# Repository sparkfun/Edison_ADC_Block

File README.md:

SparkFun Block for Intel Edison - ADC
==================================================

[*SparkFun Block for Intel Edison - ADC (DEV-13770)*](https://www.sparkfun.com/products/13770)

This card adds ADC functionality to the Edison's I<sup>2</sup>C bus. 
The ADS1015 ADC from TI provides a single 12-bit delta-sigma convertor with an analog multiplexer. 
It can be configured as a four-channel single-ended device or as a two-channel differential device.

The board has jumpers to allow selection of the I<sup>2</sup>C slave address among four different options, allowing up to four of these cards to be stacked under one Edison. 
The sampling rate is not sufficient for audio capture, at 2.2kHz, but it should be adequate for most control applications.

Repository Contents
-------------------

* **/Hardware** - Eagle design files (.brd, .sch)
* **/Production** - Production panel files (.brd)

Documentation
--------------

* **[Hookup Guide](https://learn.sparkfun.com/tutorials/sparkfun-blocks-for-intel-edison---adc-v20)** - Basic hookup guide for the Edison ADC Block.
* **[SparkFun Fritzing repo](https://github.com/sparkfun/Fritzing_Parts)** - Fritzing diagrams for SparkFun products.
* **[SparkFun 3D Model repo](https://github.com/sparkfun/3D_Models)** - 3D models of SparkFun products. 

Version History
---------------
* [v21](https://github.com/sparkfun/Edison_ADC_Block/tree/V_2.1) - Version 2.1. Currently for sale. Fixes noise on the ADC lines, adds locking header footprint. 
* [v20](https://github.com/sparkfun/Edison_ADC_Block/tree/V_2.0) - Version 2.0. Retired. 
* [v10](https://github.com/sparkfun/Edison_ADC_Block/tree/v10) - Original release. Retired.

License Information
-------------------

This product is _**open source**_! 

Please review the LICENSE.md file for license information. 

If you have any questions or concerns on licensing, please contact techsupport@sparkfun.com.

Distributed as-is; no warranty is given.

- Your friends at SparkFun.

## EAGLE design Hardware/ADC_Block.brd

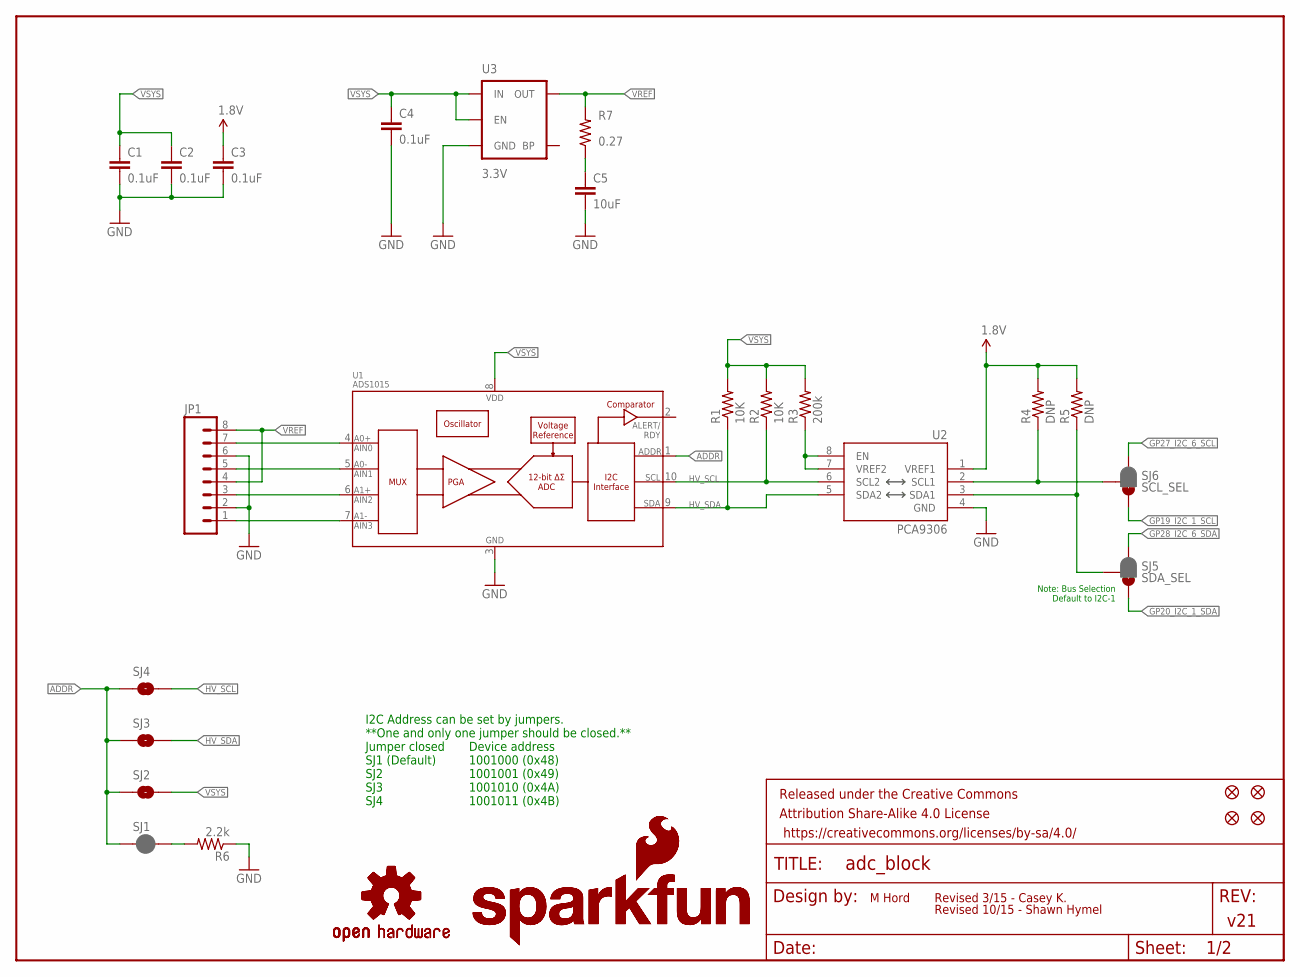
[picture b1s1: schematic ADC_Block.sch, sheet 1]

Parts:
C1, C2, C3, C4: 0.1uF; 0603-CAP
C5: 10uF; 0805-CAP
FID1, FID2, FID3, FID4: FIDUCIAL1X2; FIDUCIAL-1X2
FRAME1: FRAME-LETTER; CREATIVE_COMMONS
JP1: M08LOCK; 1X08_LOCK
LOGO1, LOGO3: SFE_LOGO_NAME_FLAME.1_INCH; SFE_LOGO_NAME_FLAME_.1
LOGO2, LOGO4: OSHW-LOGOS; OSHW-LOGO-S
R1, R2: 10K; 0603-RES
R3: 200k; 0603-RES
R4, R5: DNP; 0603-RES
R6: 2.2k; 0603-RES
R7: 0.27; 0603-RES
SJ1: JUMPER-PAD-2-NC_BY_PASTE; PAD-JUMPER-2-NC_BY_PASTE_YES_SILK
SJ2, SJ3, SJ4: JUMPER-PAD-2-NOYES_SILK; PAD-JUMPER-2-NO_YES_SILK
SJ5: SDA_SEL; PAD-HUMPER-3-1&2_NC_BY_PASTE_YES_SILK_FULL_BOX
SJ6: SCL_SEL; PAD-HUMPER-3-1&2_NC_BY_PASTE_YES_SILK_FULL_BOX
U1: ADS1015; MSOP10
U2: PCA9306; PCA9306DC-1:1
U3: 3.3V; SOT23-5

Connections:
1.8V: C3.1, R4.2, R5.2, U2.1 (VREF1); also elsewhere on the board
A0+/AIN0: JP1.7, U1.4 (AIN0)
A0-/AIN1: JP1.5, U1.5 (AIN1)
A1+/AIN2: JP1.3, U1.6 (AIN2)
A1-/AIN3: JP1.1, U1.7 (AIN3)
ADDR: SJ1.1, SJ2.1, SJ3.1, SJ4.1, U1.1 (ADDR)
GND: C1.2, C2.2, C3.2, C4.2, C5.2, JP1.2, JP1.6, R6.1, U1.3 (VSS), U2.4 (GND), U3.2 (GND); also elsewhere on the board
GP19_I2C_1_SCL: SJ6.3; also elsewhere on the board
GP20_I2C_1_SDA: SJ5.3; also elsewhere on the board
GP27_I2C_6_SCL: SJ6.1; also elsewhere on the board
GP28_I2C_6_SDA: SJ5.1; also elsewhere on the board
HV_SCL: R2.1, SJ4.2, U1.10 (SCL), U2.6 (SCL2)
HV_SDA: R1.1, SJ3.2, U1.9 (SDA), U2.5 (SDA2)
unnamed: R3.1, U2.7 (VREF2), U2.8 (EN)
unnamed: R4.1, SJ6.2, U2.2 (SCL1)
unnamed: R6.2, SJ1.2
unnamed: R5.1, SJ5.2, U2.3 (SDA1)
unnamed: C5.1, R7.1
VREF: JP1.4, JP1.8, R7.2, U3.5 (OUT)
VSYS: C1.1, C2.1, C4.1, R1.2, R2.2, R3.2, SJ2.2, U1.8 (VDD), U3.1 (IN), U3.3 (EN); also elsewhere on the board

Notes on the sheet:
I2C Address can be set by jumpers. **One and only one jumper should be closed.** Jumper closed SJ1 (Default) SJ2 SJ3 SJ4
Device address 1001000 (0x48) 1001001 (0x49) 1001010 (0x4A) 1001011 (0x4B)
v21
M Hord
Revised 3/15 - Casey K.
Note: Bus Selection Default to I2C-1
Revised 10/15 - Shawn Hymel

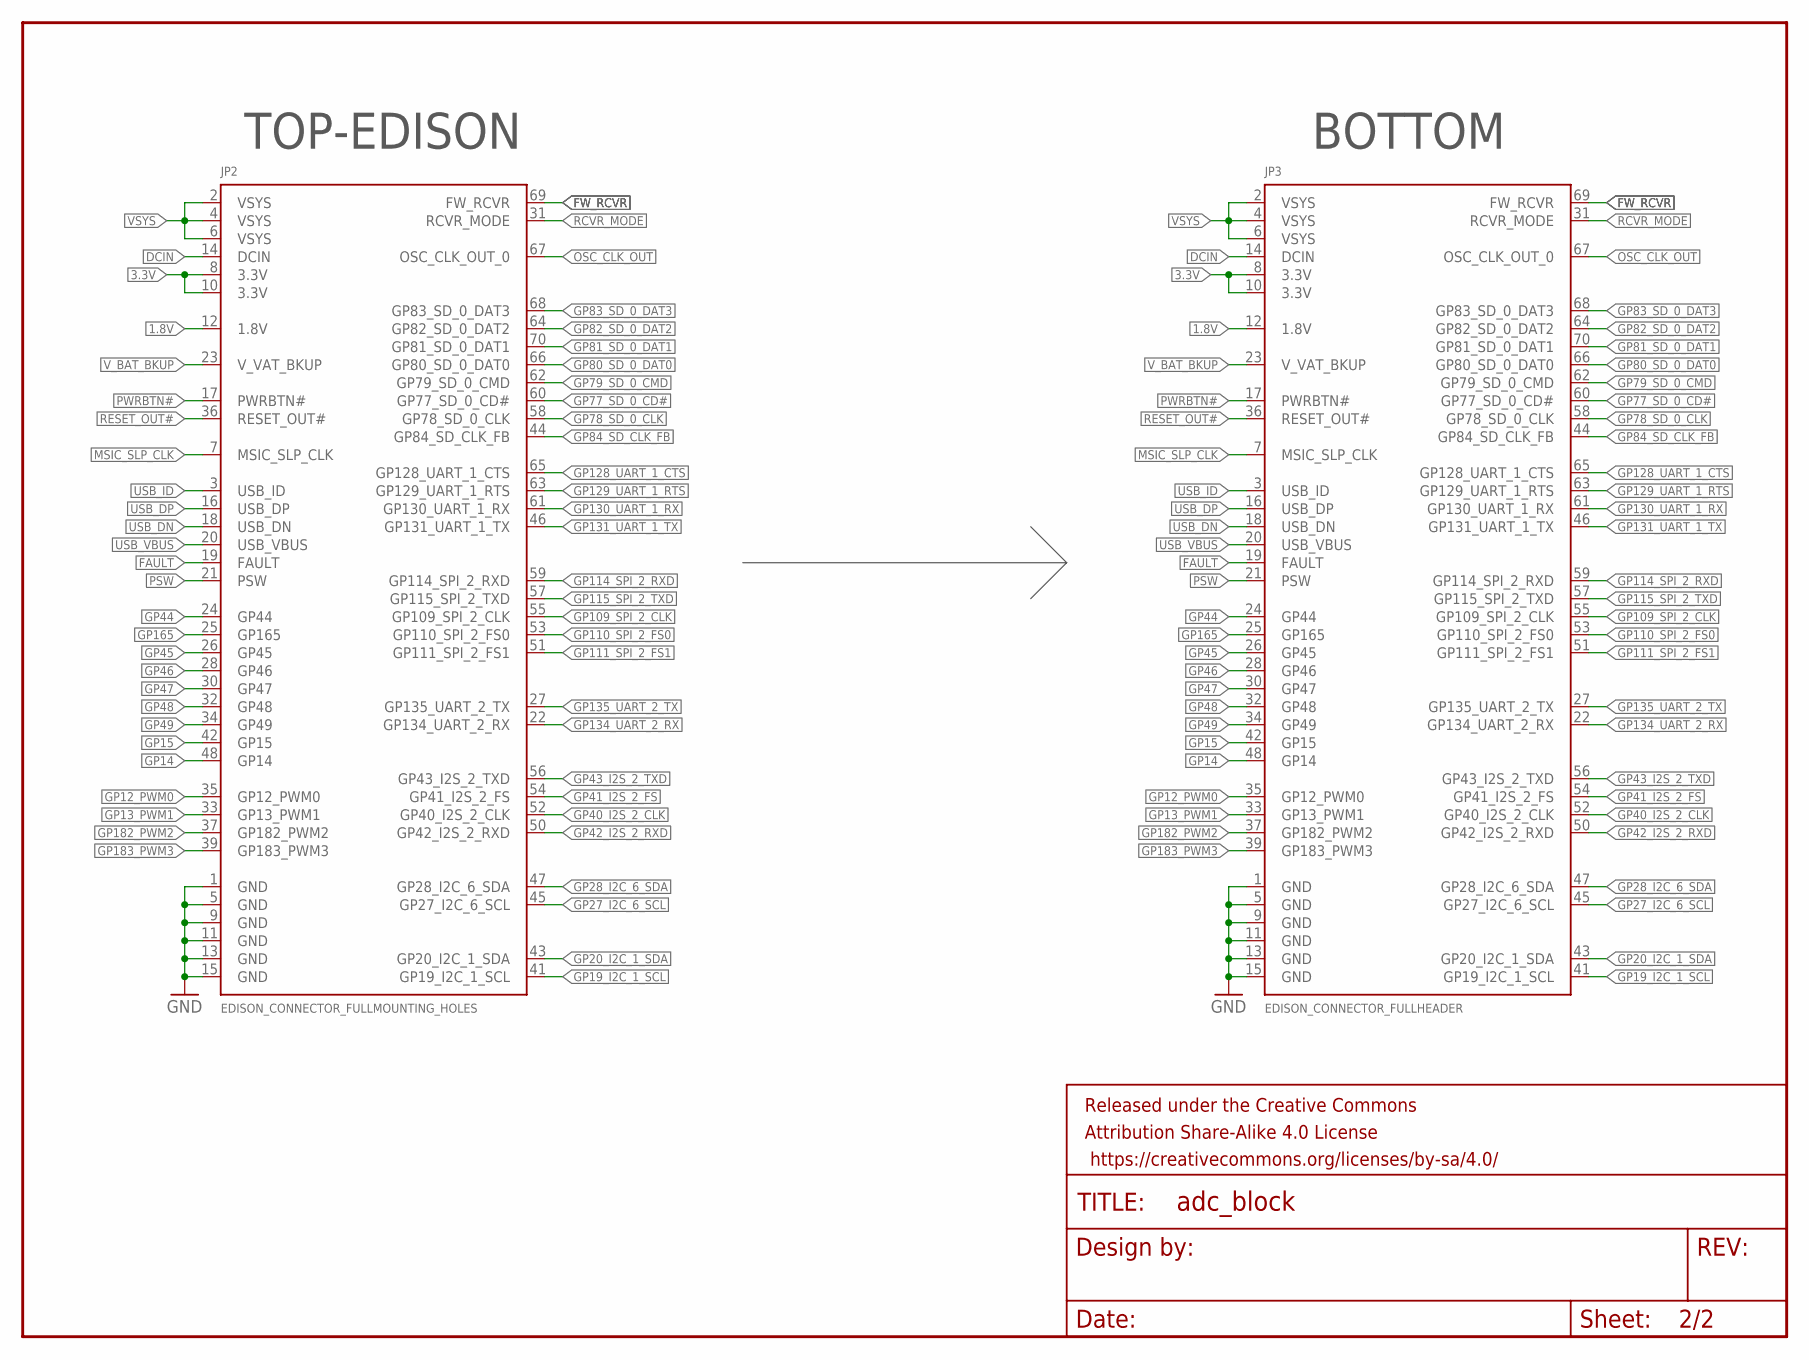
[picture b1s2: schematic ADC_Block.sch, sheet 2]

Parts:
FRAME2: FRAME-LETTER; CREATIVE_COMMONS
JP2: EDISON_CONNECTOR_FULLMOUNTING_HOLES; EDISON_DAUGHTER
JP3: EDISON_CONNECTOR_FULLHEADER; DF40C-70DP-0.4(51)

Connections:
1.8V: JP2.12 (1.8V), JP3.12 (1.8V); also elsewhere on the board
3.3V: JP2.8 (3.3V), JP2.10 (3.3V), JP3.8 (3.3V), JP3.10 (3.3V)
DCIN: JP2.14 (DCIN), JP3.14 (DCIN)
FAULT: JP2.19 (FAULT), JP3.19 (FAULT)
FW_RCVR: JP2.69 (FW_RCVR), JP3.69 (FW_RCVR)
GND: JP2.1 (GND), JP2.5 (GND), JP2.9 (GND), JP2.11 (GND), JP2.13 (GND), JP2.15 (GND), JP3.1 (GND), JP3.5 (GND), JP3.9 (GND), JP3.11 (GND), JP3.13 (GND), JP3.15 (GND); also elsewhere on the board
GP12_PWM0: JP2.35 (GP12_PWM0), JP3.35 (GP12_PWM0)
GP13_PWM1: JP2.33 (GP13_PWM1), JP3.33 (GP13_PWM1)
GP14: JP2.48 (GP14), JP3.48 (GP14)
GP15: JP2.42 (GP15), JP3.42 (GP15)
GP19_I2C_1_SCL: JP2.41 (GP19_I2C_1_SCL), JP3.41 (GP19_I2C_1_SCL); also elsewhere on the board
GP20_I2C_1_SDA: JP2.43 (GP20_I2C_1_SDA), JP3.43 (GP20_I2C_1_SDA); also elsewhere on the board
GP27_I2C_6_SCL: JP2.45 (GP27_I2C_6_SCL), JP3.45 (GP27_I2C_6_SCL); also elsewhere on the board
GP28_I2C_6_SDA: JP2.47 (GP28_I2C_6_SDA), JP3.47 (GP28_I2C_6_SDA); also elsewhere on the board
GP40_I2S_2_CLK: JP2.52 (GP40_I2S_2_CLK), JP3.52 (GP40_I2S_2_CLK)
GP41_I2S_2_FS: JP2.54 (GP41_I2S_2_FS), JP3.54 (GP41_I2S_2_FS)
GP42_I2S_2_RXD: JP2.50 (GP42_I2S_2_RXD), JP3.50 (GP42_I2S_2_RXD)
GP43_I2S_2_TXD: JP2.56 (GP43_I2S_2_TXD), JP3.56 (GP43_I2S_2_TXD)
GP44: JP2.24 (GP44), JP3.24 (GP44)
GP45: JP2.26 (GP45), JP3.26 (GP45)
GP46: JP2.28 (GP46), JP3.28 (GP46)
GP47: JP2.30 (GP47), JP3.30 (GP47)
GP48: JP2.32 (GP48), JP3.32 (GP48)
GP49: JP2.34 (GP49), JP3.34 (GP49)
GP77_SD_0_CD#: JP2.60 (GP77_SD_0_CD#), JP3.60 (GP77_SD_0_CD#)
GP78_SD_0_CLK: JP2.58 (GP78_SD_0_CLK), JP3.58 (GP78_SD_0_CLK)
GP79_SD_0_CMD: JP2.62 (GP79_SD_0_CMD), JP3.62 (GP79_SD_0_CMD)
GP80_SD_0_DAT0: JP2.66 (GP80_SD_0_DAT0), JP3.66 (GP80_SD_0_DAT0)
GP81_SD_0_DAT1: JP2.70 (GP81_SD_0_DAT1), JP3.70 (GP81_SD_0_DAT1)
GP82_SD_0_DAT2: JP2.64 (GP82_SD_0_DAT2), JP3.64 (GP82_SD_0_DAT2)
GP83_SD_0_DAT3: JP2.68 (GP83_SD_0_DAT3), JP3.68 (GP83_SD_0_DAT3)
GP84_SD_CLK_FB: JP2.44 (GP84_SD_CLK_FB), JP3.44 (GP84_SD_CLK_FB)
GP109_SPI_2_CLK: JP2.55 (GP109_SPI_2_CLK), JP3.55 (GP109_SPI_2_CLK)
GP110_SPI_2_FS0: JP2.53 (GP110_SPI_2_FS0), JP3.53 (GP110_SPI_2_FS0)
GP111_SPI_2_FS1: JP2.51 (GP111_SPI_2_FS1), JP3.51 (GP111_SPI_2_FS1)
GP114_SPI_2_RXD: JP2.59 (GP114_SPI_2_RXD), JP3.59 (GP114_SPI_2_RXD)
GP115_SPI_2_TXD: JP2.57 (GP115_SPI_2_TXD), JP3.57 (GP115_SPI_2_TXD)
GP128_UART_1_CTS: JP2.65 (GP128_UART_1_CTS), JP3.65 (GP128_UART_1_CTS)
GP129_UART_1_RTS: JP2.63 (GP129_UART_1_RTS), JP3.63 (GP129_UART_1_RTS)
GP130_UART_1_RX: JP2.61 (GP130_UART_1_RX), JP3.61 (GP130_UART_1_RX)
GP131_UART_1_TX: JP2.46 (GP131_UART_1_TX), JP3.46 (GP131_UART_1_TX)
GP134_UART_2_RX: JP2.22 (GP134_UART_2_RX), JP3.22 (GP134_UART_2_RX)
GP135_UART_2_TX: JP2.27 (GP135_UART_2_TX), JP3.27 (GP135_UART_2_TX)
GP165: JP2.25 (GP165), JP3.25 (GP165)
GP182_PWM2: JP2.37 (GP182_PWM2), JP3.37 (GP182_PWM2)
GP183_PWM3: JP2.39 (GP183_PWM3), JP3.39 (GP183_PWM3)
MSIC_SLP_CLK: JP2.7 (MSIC_SLP_CLK), JP3.7 (MSIC_SLP_CLK)
OSC_CLK_OUT: JP2.67 (OSC_CLK_OUT_0), JP3.67 (OSC_CLK_OUT_0)
PSW: JP2.21 (PSW), JP3.21 (PSW)
PWRBTN#: JP2.17 (PWRBTN#), JP3.17 (PWRBTN#)
RCVR_MODE: JP2.31 (RCVR_MODE), JP3.31 (RCVR_MODE)
RESET_OUT#: JP2.36 (RESET_OUT#), JP3.36 (RESET_OUT#)
USB_DN: JP2.18 (USB_DN), JP3.18 (USB_DN)
USB_DP: JP2.16 (USB_DP), JP3.16 (USB_DP)
USB_ID: JP2.3 (USB_ID), JP3.3 (USB_ID)
USB_VBUS: JP2.20 (USB_VBUS), JP3.20 (USB_VBUS)
VSYS: JP2.2 (VSYS), JP2.4 (VSYS), JP2.6 (VSYS), JP3.2 (VSYS), JP3.4 (VSYS), JP3.6 (VSYS); also elsewhere on the board
V_BAT_BKUP: JP2.23 (V_VAT_BKUP), JP3.23 (V_VAT_BKUP)

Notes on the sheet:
TOP-EDISON
BOTTOM

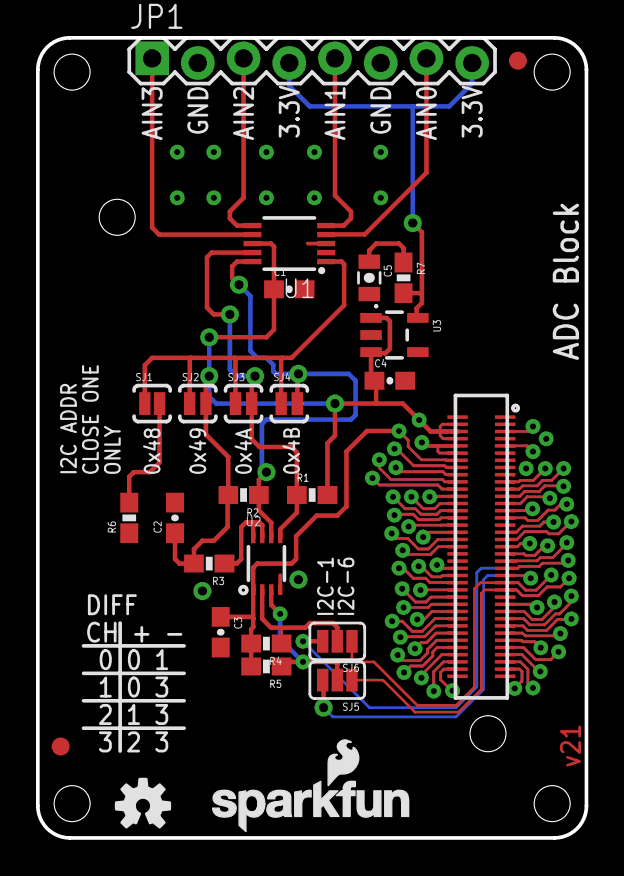
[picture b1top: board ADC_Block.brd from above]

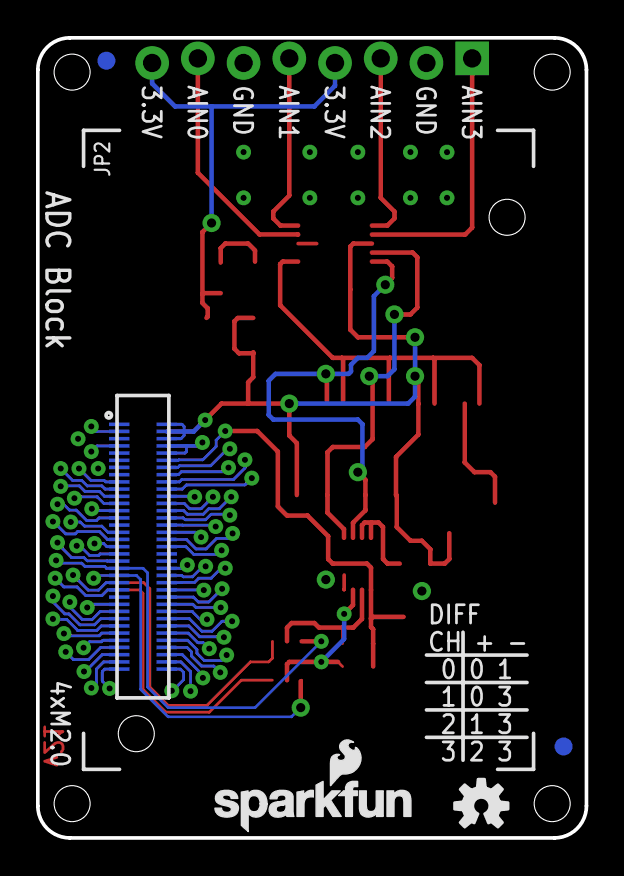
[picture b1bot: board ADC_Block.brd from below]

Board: 2 copper layers, 30.5 x 44.5 mm, 34 parts (6 on the bottom side), 71 nets.

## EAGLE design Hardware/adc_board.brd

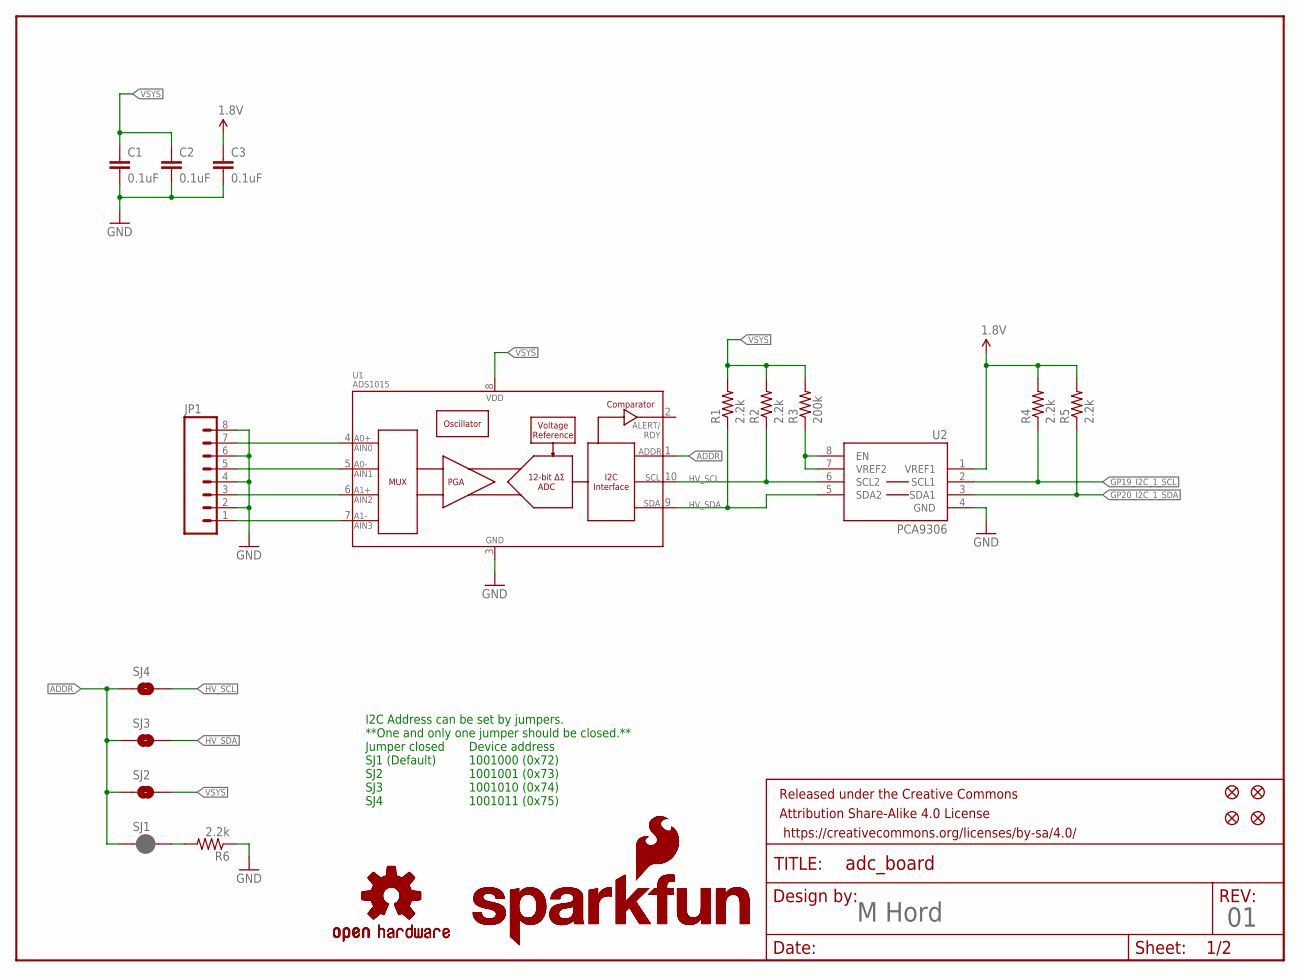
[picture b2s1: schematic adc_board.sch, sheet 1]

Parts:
C1, C2, C3: 0.1uF; 0603-CAP
FID1, FID2, FID3, FID4: FIDUCIAL1X2; FIDUCIAL-1X2
FRAME1: FRAME-LETTER; CREATIVE_COMMONS
JP1: M081X08; 1X08
LOGO1, LOGO3: SFE_LOGO_NAME_FLAME.1_INCH; SFE_LOGO_NAME_FLAME_.1
LOGO2, LOGO4: OSHW-LOGOS; OSHW-LOGO-S
R1, R2, R4, R5, R6: 2.2k; 0603-RES
R3: 200k; 0603-RES
SJ1: JUMPER-PAD-2-NC_BY_PASTE; PAD-JUMPER-2-NC_BY_PASTE_YES_SILK
SJ2, SJ3, SJ4: JUMPER-PAD-2-NOYES_SILK; PAD-JUMPER-2-NO_YES_SILK
U1: ADS1015; MSOP10
U2: PCA9306; PCA9306DC-1:1

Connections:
1.8V: C3.1, R4.2, R5.2, U2.1 (VREF1); also elsewhere on the board
A0+/AIN0: JP1.7, U1.4 (AIN0)
A0-/AIN1: JP1.5, U1.5 (AIN1)
A1+/AIN2: JP1.3, U1.6 (AIN2)
A1-/AIN3: JP1.1, U1.7 (AIN3)
ADDR: SJ1.1, SJ2.1, SJ3.1, SJ4.1, U1.1 (ADDR)
GND: C1.2, C2.2, C3.2, JP1.2, JP1.4, JP1.6, JP1.8, R6.1, U1.3 (VSS), U2.4 (GND); also elsewhere on the board
GP19_I2C_1_SCL: R4.1, U2.2 (SCL1); also elsewhere on the board
GP20_I2C_1_SDA: R5.1, U2.3 (SDA1); also elsewhere on the board
HV_SCL: R2.1, SJ4.2, U1.10 (SCL), U2.6 (SCL2)
HV_SDA: R1.1, SJ3.2, U1.9 (SDA), U2.5 (SDA2)
unnamed: R3.1, U2.7 (VREF2), U2.8 (EN)
unnamed: R6.2, SJ1.2
VSYS: C1.1, C2.1, R1.2, R2.2, R3.2, SJ2.2, U1.8 (VDD); also elsewhere on the board

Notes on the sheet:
I2C Address can be set by jumpers. **One and only one jumper should be closed.** Jumper closed SJ1 (Default) SJ2 SJ3 SJ4
Device address 1001000 (0x72) 1001001 (0x73) 1001010 (0x74) 1001011 (0x75)
M Hord

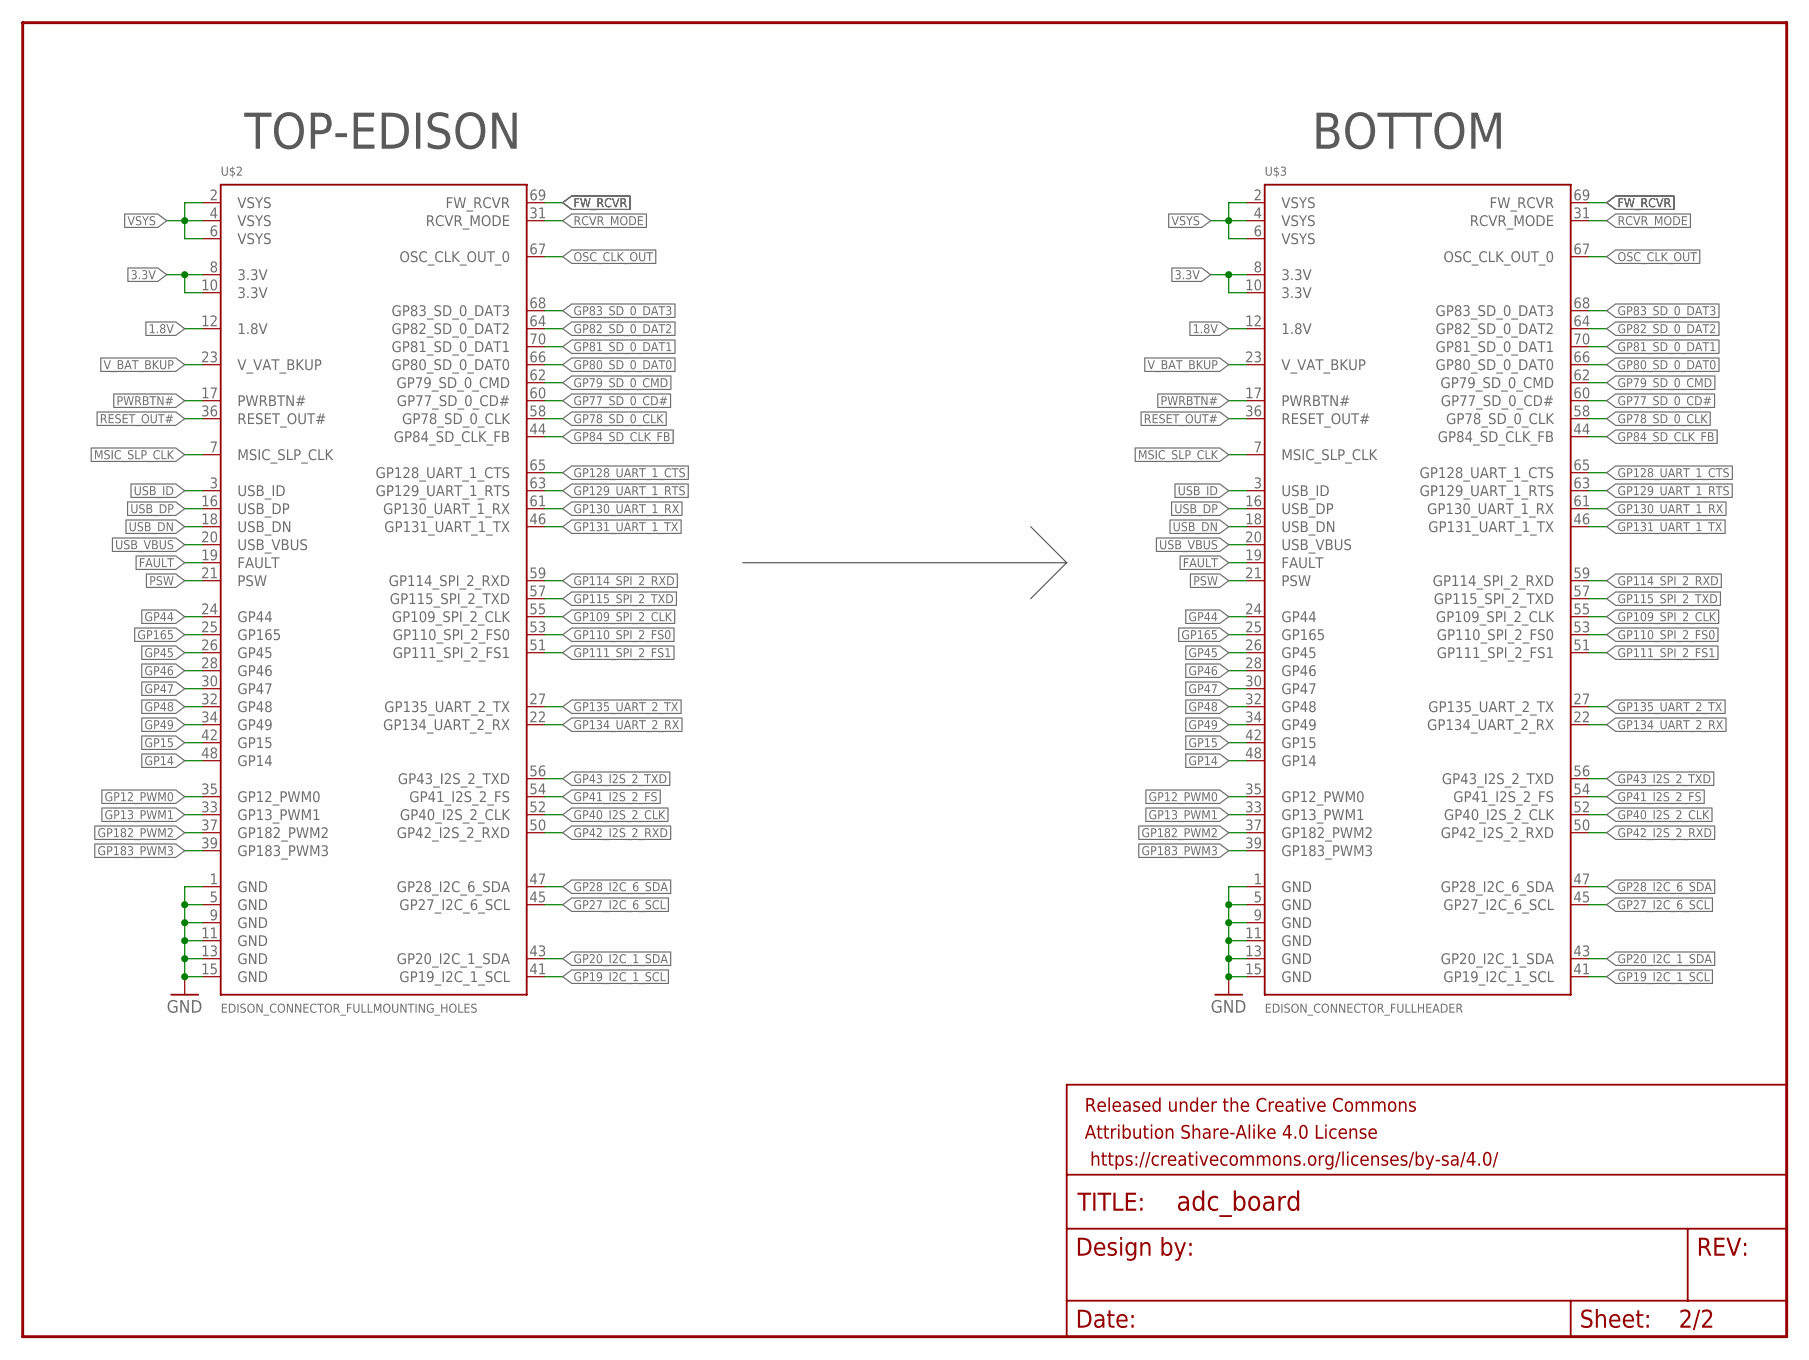
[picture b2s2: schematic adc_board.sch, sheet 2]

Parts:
FRAME2: FRAME-LETTER; CREATIVE_COMMONS
U$2: EDISON_CONNECTOR_FULLMOUNTING_HOLES; EDISON_DAUGHTER
U$3: EDISON_CONNECTOR_FULLHEADER; DF40C-70DP-0.4(51)

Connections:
1.8V: U$2.12 (1.8V), U$3.12 (1.8V); also elsewhere on the board
3.3V: U$2.8 (3.3V), U$2.10 (3.3V), U$3.8 (3.3V), U$3.10 (3.3V)
FAULT: U$2.19 (FAULT), U$3.19 (FAULT)
FW_RCVR: U$2.69 (FW_RCVR), U$3.69 (FW_RCVR)
GND: U$2.1 (GND), U$2.5 (GND), U$2.9 (GND), U$2.11 (GND), U$2.13 (GND), U$2.15 (GND), U$3.1 (GND), U$3.5 (GND), U$3.9 (GND), U$3.11 (GND), U$3.13 (GND), U$3.15 (GND); also elsewhere on the board
GP12_PWM0: U$2.35 (GP12_PWM0), U$3.35 (GP12_PWM0)
GP13_PWM1: U$2.33 (GP13_PWM1), U$3.33 (GP13_PWM1)
GP14: U$2.48 (GP14), U$3.48 (GP14)
GP15: U$2.42 (GP15), U$3.42 (GP15)
GP19_I2C_1_SCL: U$2.41 (GP19_I2C_1_SCL), U$3.41 (GP19_I2C_1_SCL); also elsewhere on the board
GP20_I2C_1_SDA: U$2.43 (GP20_I2C_1_SDA), U$3.43 (GP20_I2C_1_SDA); also elsewhere on the board
GP27_I2C_6_SCL: U$2.45 (GP27_I2C_6_SCL), U$3.45 (GP27_I2C_6_SCL)
GP28_I2C_6_SDA: U$2.47 (GP28_I2C_6_SDA), U$3.47 (GP28_I2C_6_SDA)
GP40_I2S_2_CLK: U$2.52 (GP40_I2S_2_CLK), U$3.52 (GP40_I2S_2_CLK)
GP41_I2S_2_FS: U$2.54 (GP41_I2S_2_FS), U$3.54 (GP41_I2S_2_FS)
GP42_I2S_2_RXD: U$2.50 (GP42_I2S_2_RXD), U$3.50 (GP42_I2S_2_RXD)
GP43_I2S_2_TXD: U$2.56 (GP43_I2S_2_TXD), U$3.56 (GP43_I2S_2_TXD)
GP44: U$2.24 (GP44), U$3.24 (GP44)
GP45: U$2.26 (GP45), U$3.26 (GP45)
GP46: U$2.28 (GP46), U$3.28 (GP46)
GP47: U$2.30 (GP47), U$3.30 (GP47)
GP48: U$2.32 (GP48), U$3.32 (GP48)
GP49: U$2.34 (GP49), U$3.34 (GP49)
GP77_SD_0_CD#: U$2.60 (GP77_SD_0_CD#), U$3.60 (GP77_SD_0_CD#)
GP78_SD_0_CLK: U$2.58 (GP78_SD_0_CLK), U$3.58 (GP78_SD_0_CLK)
GP79_SD_0_CMD: U$2.62 (GP79_SD_0_CMD), U$3.62 (GP79_SD_0_CMD)
GP80_SD_0_DAT0: U$2.66 (GP80_SD_0_DAT0), U$3.66 (GP80_SD_0_DAT0)
GP81_SD_0_DAT1: U$2.70 (GP81_SD_0_DAT1), U$3.70 (GP81_SD_0_DAT1)
GP82_SD_0_DAT2: U$2.64 (GP82_SD_0_DAT2), U$3.64 (GP82_SD_0_DAT2)
GP83_SD_0_DAT3: U$2.68 (GP83_SD_0_DAT3), U$3.68 (GP83_SD_0_DAT3)
GP84_SD_CLK_FB: U$2.44 (GP84_SD_CLK_FB), U$3.44 (GP84_SD_CLK_FB)
GP109_SPI_2_CLK: U$2.55 (GP109_SPI_2_CLK), U$3.55 (GP109_SPI_2_CLK)
GP110_SPI_2_FS0: U$2.53 (GP110_SPI_2_FS0), U$3.53 (GP110_SPI_2_FS0)
GP111_SPI_2_FS1: U$2.51 (GP111_SPI_2_FS1), U$3.51 (GP111_SPI_2_FS1)
GP114_SPI_2_RXD: U$2.59 (GP114_SPI_2_RXD), U$3.59 (GP114_SPI_2_RXD)
GP115_SPI_2_TXD: U$2.57 (GP115_SPI_2_TXD), U$3.57 (GP115_SPI_2_TXD)
GP128_UART_1_CTS: U$2.65 (GP128_UART_1_CTS), U$3.65 (GP128_UART_1_CTS)
GP129_UART_1_RTS: U$2.63 (GP129_UART_1_RTS), U$3.63 (GP129_UART_1_RTS)
GP130_UART_1_RX: U$2.61 (GP130_UART_1_RX), U$3.61 (GP130_UART_1_RX)
GP131_UART_1_TX: U$2.46 (GP131_UART_1_TX), U$3.46 (GP131_UART_1_TX)
GP134_UART_2_RX: U$2.22 (GP134_UART_2_RX), U$3.22 (GP134_UART_2_RX)
GP135_UART_2_TX: U$2.27 (GP135_UART_2_TX), U$3.27 (GP135_UART_2_TX)
GP165: U$2.25 (GP165), U$3.25 (GP165)
GP182_PWM2: U$2.37 (GP182_PWM2), U$3.37 (GP182_PWM2)
GP183_PWM3: U$2.39 (GP183_PWM3), U$3.39 (GP183_PWM3)
MSIC_SLP_CLK: U$2.7 (MSIC_SLP_CLK), U$3.7 (MSIC_SLP_CLK)
OSC_CLK_OUT: U$2.67 (OSC_CLK_OUT_0), U$3.67 (OSC_CLK_OUT_0)
PSW: U$2.21 (PSW), U$3.21 (PSW)
PWRBTN#: U$2.17 (PWRBTN#), U$3.17 (PWRBTN#)
RCVR_MODE: U$2.31 (RCVR_MODE), U$3.31 (RCVR_MODE)
RESET_OUT#: U$2.36 (RESET_OUT#), U$3.36 (RESET_OUT#)
USB_DN: U$2.18 (USB_DN), U$3.18 (USB_DN)
USB_DP: U$2.16 (USB_DP), U$3.16 (USB_DP)
USB_ID: U$2.3 (USB_ID), U$3.3 (USB_ID)
USB_VBUS: U$2.20 (USB_VBUS), U$3.20 (USB_VBUS)
VSYS: U$2.2 (VSYS), U$2.4 (VSYS), U$2.6 (VSYS), U$3.2 (VSYS), U$3.4 (VSYS), U$3.6 (VSYS); also elsewhere on the board
V_BAT_BKUP: U$2.23 (V_VAT_BKUP), U$3.23 (V_VAT_BKUP)

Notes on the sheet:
TOP-EDISON
BOTTOM

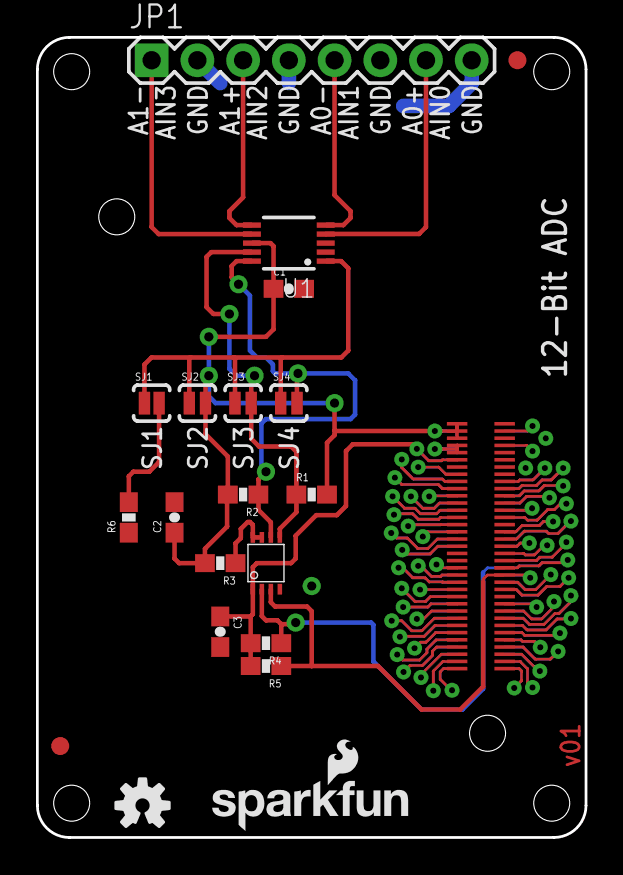
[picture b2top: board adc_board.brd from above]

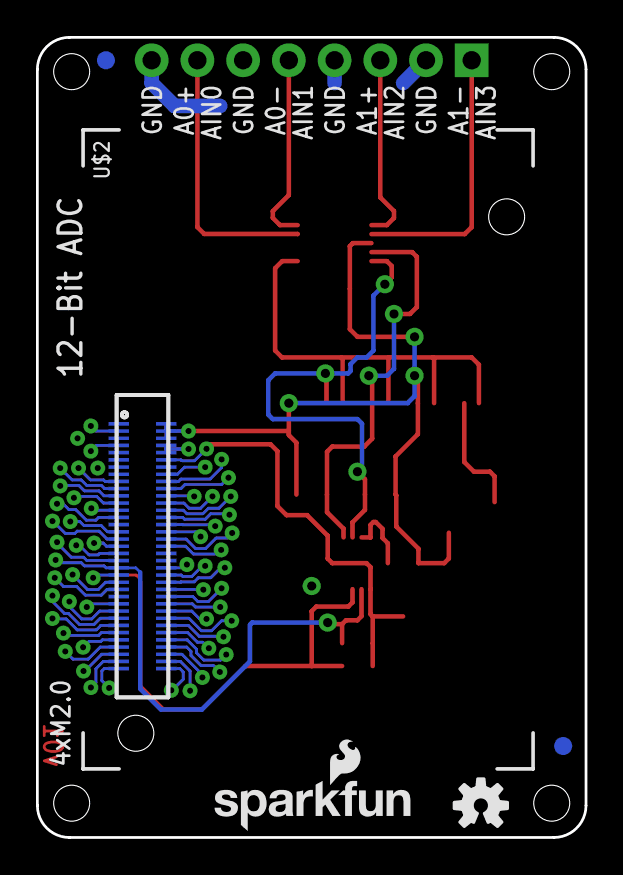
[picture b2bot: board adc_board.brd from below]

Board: 2 copper layers, 30.5 x 44.5 mm, 28 parts (6 on the bottom side), 66 nets.

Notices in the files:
parts and their libraries:
SparkFun-Aesthetics: Licensing: Creative Commons ShareAlike 4.0 International - https://creativecommons.org/licenses/by-sa/4.0
SparkFun-Aesthetics: Released under the Creative Commons Attribution Share-Alike 4.0 License
SparkFun-Aesthetics: https://creativecommons.org/licenses/by-sa/4.0
